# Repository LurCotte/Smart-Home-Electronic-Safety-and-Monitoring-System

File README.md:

# 🔌 Smart Home Electronic Safety and Monitoring System

## Team Member

## 📘 Deskripsi Proyek

Proyek ini bertujuan untuk mengembangkan **sistem automasi rumah pintar (Smart Home Automation System)** yang dapat memantau dan mengontrol peralatan elektronik secara real-time. Sistem ini juga dilengkapi dengan fitur **auto cut-off** untuk menjaga peralatan rumah tangga dari fluktuasi tegangan yang berasal dari jaringan listrik PLN.

## 🎯 Tujuan

- Mengontrol peralatan elektronik rumah secara dari satu titik pusat.
- Memantau konsumsi energi listrik dan menghitung biaya secara akurat.
- Melindungi perangkat dari overvoltage atau undervoltage melalui fitur auto cut-off.

## Video Iklan
https://vt.tiktok.com/ZSk2q9HfW/

## 🧠 Komponen Utama

| Komponen       | Fungsi                                                                 |
|----------------|------------------------------------------------------------------------|
| Arduino Mega   | Mikrokontroler utama yang mengatur komunikasi dan pengolahan data.     |
| ACS712         | Sensor arus untuk mengukur konsumsi arus listrik.                      |
| ZMPT101B       | Sensor tegangan AC untuk memantau tegangan dari sumber PLN.            |
| Relay SPDT     | Saklar untuk mengontrol perangkat listrik seperti lampu.      |
| MCB 1 Phase    | Proteksi arus lebih dan hubung singkat memutus aliran saat overload.  |
| Sensor Tambahan| Sensor-sensor lain untuk mendukung fungsi Smart Home tambahan.         |

## 🔗 Komunikasi Sistem

Sistem menggunakan **komunikasi UART TTL** untuk mentransmisikan data antar perangkat dan sensor secara real-time. Arduino Mega memproses input dari sensor, lalu mengambil tindakan sesuai logika program.

## ⚡ Fitur Utama

- **Auto Cut-Off:** Memutus sambungan perangkat jika terjadi fluktuasi tegangan di luar ambang batas aman.
- **Monitoring Energi:** Penggunaan sensor ACS712 dan ZMPT101B untuk memantau konsumsi arus dan tegangan secara real-time.
- **Kontrol Perangkat Secara Terpusat:** Semua perangkat bisa dikontrol dari satu titik pusat melalui Komputer/laptop via UART.

## 🧩 Penjelasan Alur Sistem

- **Kabel fasa dan netral dari MCB PLN** terlebih dahulu masuk ke **input sensor ZMPT101B**. Sensor ini digunakan untuk membaca nilai tegangan dalam bentuk ADC (Analog to Digital Converter) yang kemudian akan diumpankan ke **pin analog mikrokontroler AVR**.

- **Mikrokontroler AVR** berkomunikasi dengan **laptop melalui komunikasi serial UART**, yang berfungsi sebagai antarmuka dan pusat kontrol untuk mengaktifkan atau menonaktifkan perangkat elektronik dari satu tempat.

- Pada **relay 5V**, pin **pole (common)** dihubungkan ke kabel fasa dari MCB PLN, pin **NO (Normally Open)** dihubungkan ke input MCB 1 phase, dan pin **coil** dihubungkan ke **pin output dari mikrokontroler AVR**.

- Jika **mikrokontroler AVR menerima perintah aktivasi dari laptop**, maka ia akan mengaktifkan pin output yang telah ditentukan, sehingga mengaktifkan relay dan menyebabkan perangkat elektronik menyala. Namun, hal ini hanya akan terjadi **jika tidak terdeteksi adanya fluktuasi tegangan atau hubung singkat**.

- **Perintah pengaktifan perangkat elektronik tidak akan diproses jika terjadi fluktuasi tegangan**, karena fungsi pendeteksi fluktuasi memiliki prioritas lebih tinggi. 

- Selain itu, jika terjadi **hubung singkat**, maka aktivasi perangkat tidak dapat dilakukan karena **MCB secara otomatis akan melakukan pemutusan arus (OFF)** untuk proteksi sistem.

- **Sensor ACS712** digunakan untuk membaca arus listrik yang kemudian akan digunakan untuk **perhitungan daya listrik (Watt)** secara real-time.

## 📊 Mind Map, Flowchart dan Diagram Blok

*Mind Map.*

*Flowchart.*

*Diagram Blok Sistem.*

*Tampilan GUI Python*

## 🚀 Pengembangan Selanjutnya

- Integrasi dengan koneksi WiFi (ESP8266/ESP32) untuk kontrol via aplikasi mobile.
- Dashboard berbasis web untuk pemantauan konsumsi daya secara grafis.
- Otomatisasi berdasarkan waktu, cuaca, atau sensor gerak.

## 📁 Struktur Direktori (Opsional)
```bash
SmartHome-Automation/
│
├── src/                      # Kode program Arduino
├── images/                   # Diagram dan flowchart sistem
│   ├── block_diagram.png
│   └── flowchart_program.png
├── README.md                 # Dokumentasi proyek
└── docs/                     # Panduan penggunaan & pengembangan

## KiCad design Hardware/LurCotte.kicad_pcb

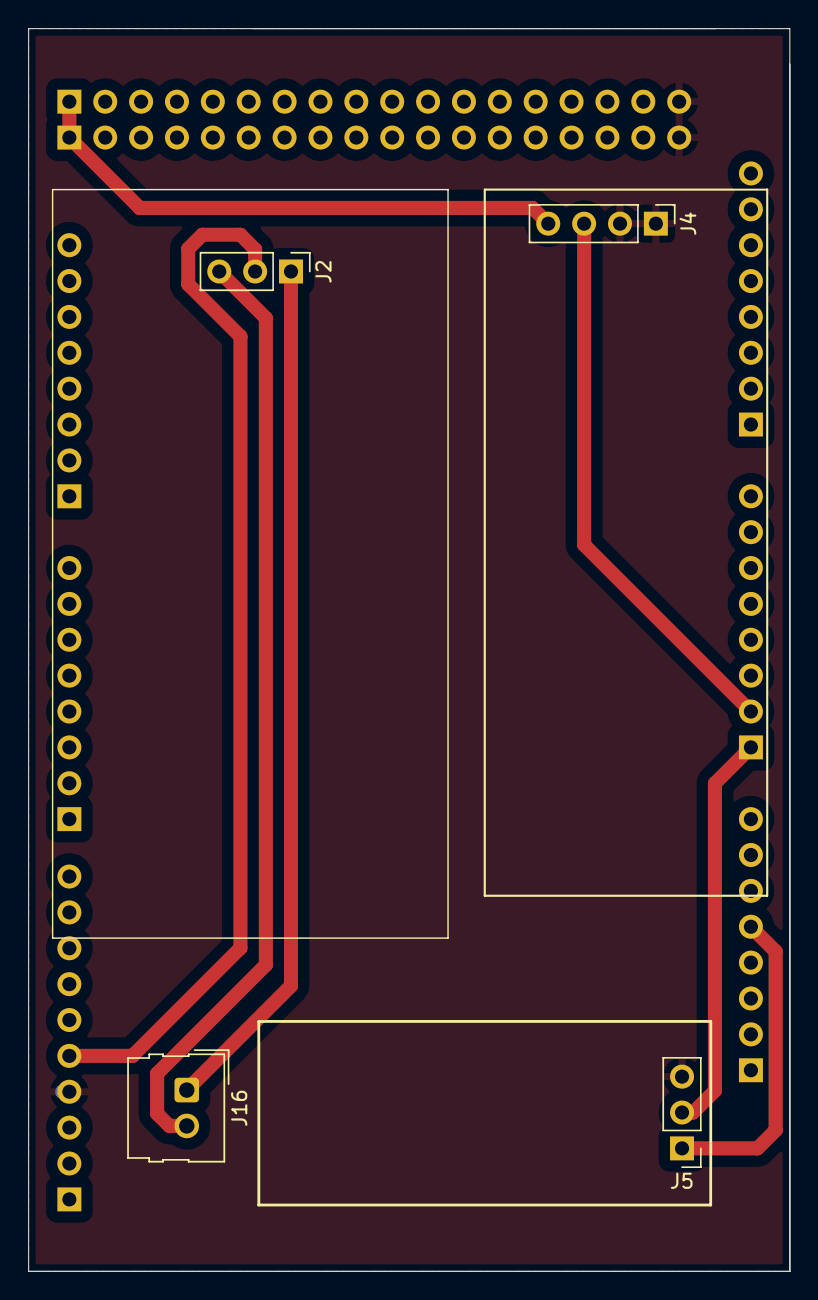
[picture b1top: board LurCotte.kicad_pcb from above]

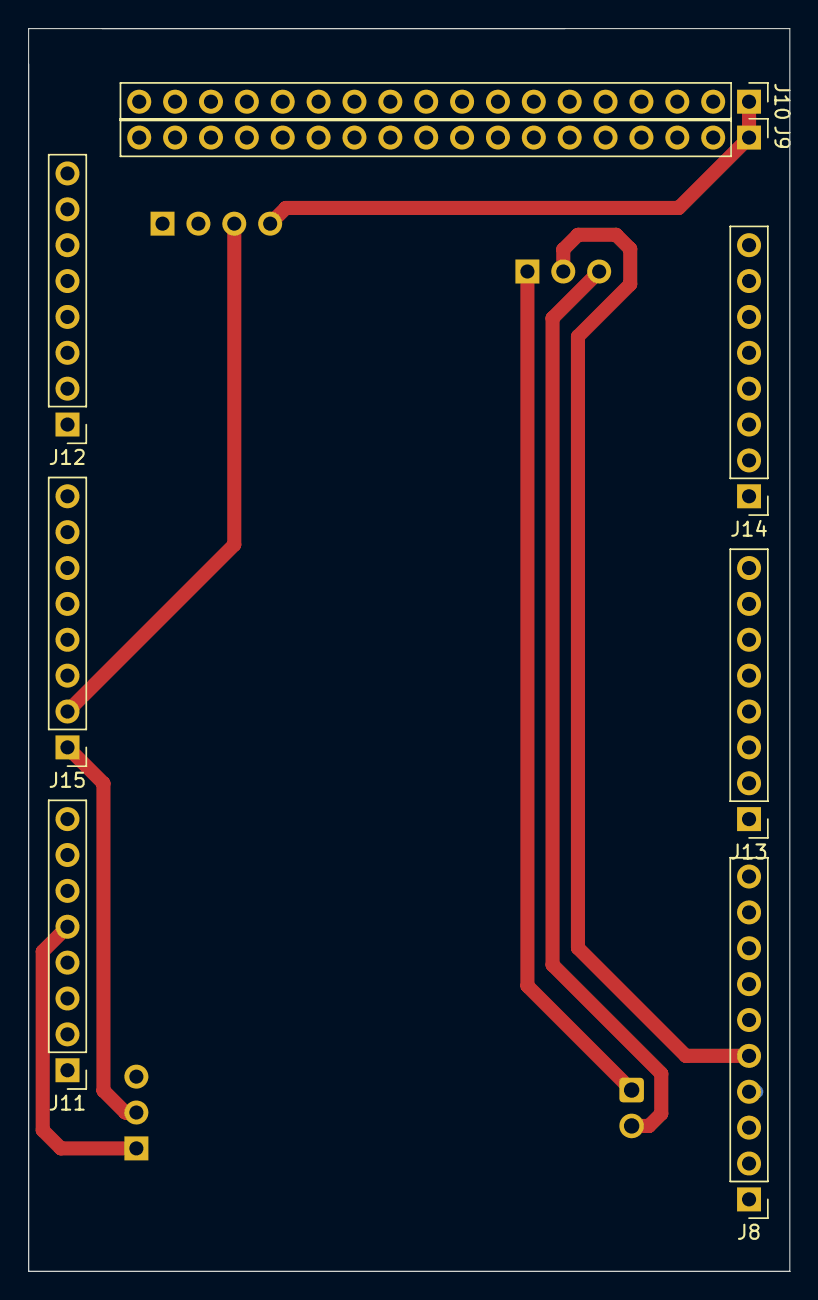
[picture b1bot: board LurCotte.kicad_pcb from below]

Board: 2 copper layers, 53.9 x 88.0 mm, 12 parts (8 on the bottom side), 7 nets.

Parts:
J2: Relay Module; PinHeader_1x03_P2.54mm_Vertical
J4: ZMPT101b; PinHeader_1x04_P2.54mm_Vertical
J5: ACS712; PinHeader_1x03_P2.54mm_Vertical
J8: Conn_01x10_Pin; PinHeader_1x10_P2.54mm_Vertical
J9, J10: Conn_01x18_Pin; PinHeader_1x18_P2.54mm_Vertical
J11, J12, J13, J14, J15: Conn_01x08_Pin; PinHeader_1x08_P2.54mm_Vertical
J16: Conn_01x02; Molex_SL_171971-0002_1x02_P2.54mm_Vertical

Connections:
+5V: J4.4, J5.1, J9.1, J10.1, J11.5
A0: J5.2, J15.1
A1: J4.3, J15.2
D13: J2.2, J8.5
GND: J4.1, J4.2, J5.3, J8.4, J9.18, J10.18
GNDPWR: J2.3, J16.2
VCC: J2.1, J16.1

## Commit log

2025-05-09 Create week 4
2025-05-18 Add SCH, BOARD, 3d Hardware
2025-05-18 Add SCH.png
2025-05-18 Create 4
2025-05-18 Progress Week 4 "Hardware & Mekanik"
2025-05-20 Add PNG Board
2025-05-20 ADD 3D
2025-06-02 Create AVR
2025-06-02 Create Penjelasan Inisialisasi program
2025-06-02 Create Variabel Pin dan Parameter Sistem
2025-06-02 Create Batasan Parameter dan Tarif Energi
2025-06-02 Create Variabel Monitoring
2025-06-02 Create Variabel Status Sistem
2025-06-02 Create Buffer Status Pemulihan
2025-06-02 Create Deteksi Arus Pendek (Short Circuit)
2025-06-02 Create Deteksi Overvoltage
2025-06-02 Create Deteksi Undervoltage
2025-06-02 Create Deteksi Fluktuasi Tegangan
2025-06-02 Create Saat Proteksi Aktif: Relay OFF dan Masuk Mode Pemulihan
2025-06-02 Create Mengecek Apakah Sistem Sedang dalam Pemulihan
2025-06-02 Create Mengisi Buffer Monitoring Kestabilan
2025-06-02 Create Logika Mengecek Kestabilan
2025-06-02 Create Setelah Buffer Terisi: Evaluasi Hasil
2025-06-02 Create Jika Semua Aman: Relay ON dan Keluar dari Mode Pemulihan
2025-06-02 Create Ringkasan Alur Pemulihan Setelah Proteksi
2025-06-02 edit typo.md
2025-06-02 Create Perhitungan Energi, Biaya, dan Penyimpanan EEPROM
2025-06-03 Add schematic
